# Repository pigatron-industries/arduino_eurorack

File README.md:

# Arduino Eurorack

Utilities for creating Eurorack modules using Arduino devices.

Tested with the following devices, but will likely work with any 3.3v logic level device (may require changes for a 5v logic level):

    Teensy LC / 4.0 / 4.1
    Electrosmith Daisy

## Documentation

[Documentation](https://pigatron-industries.github.io/arduino_eurorack/)

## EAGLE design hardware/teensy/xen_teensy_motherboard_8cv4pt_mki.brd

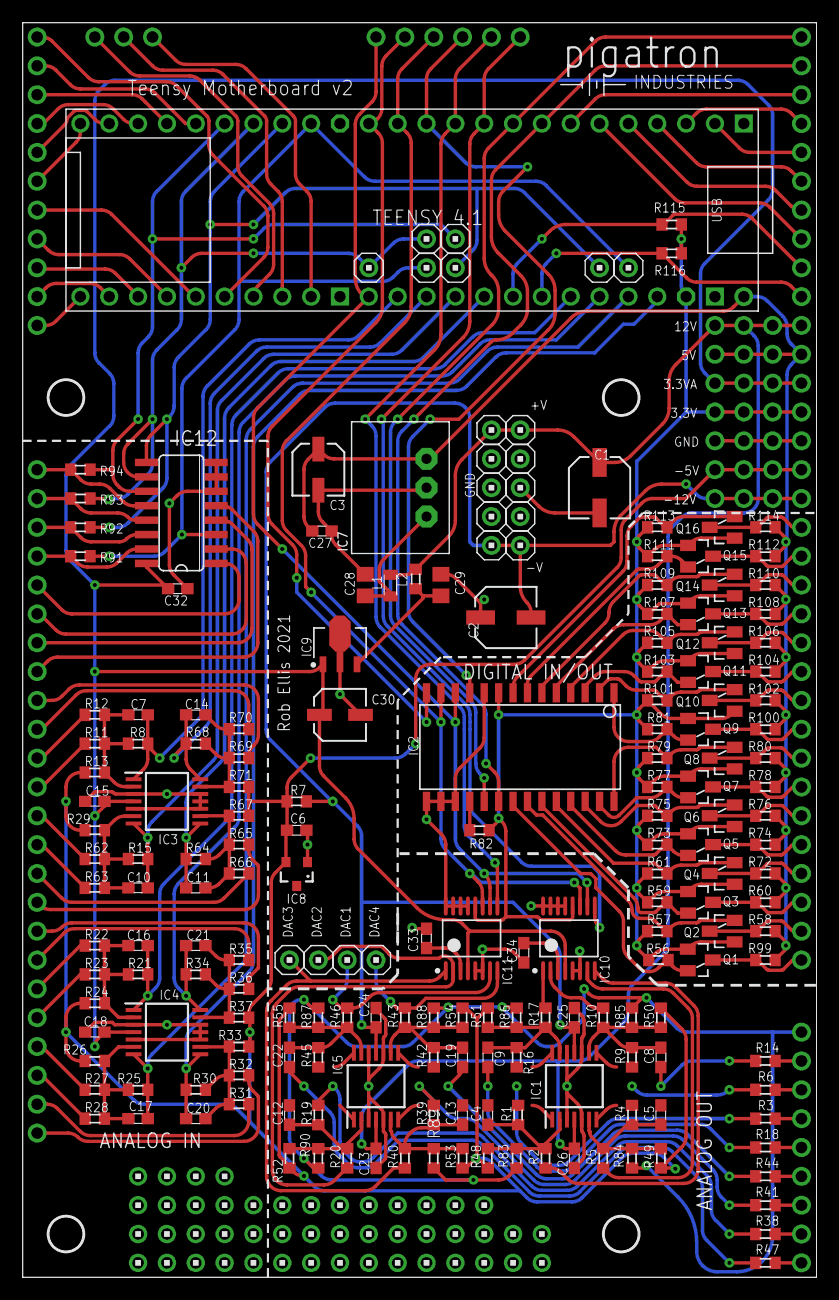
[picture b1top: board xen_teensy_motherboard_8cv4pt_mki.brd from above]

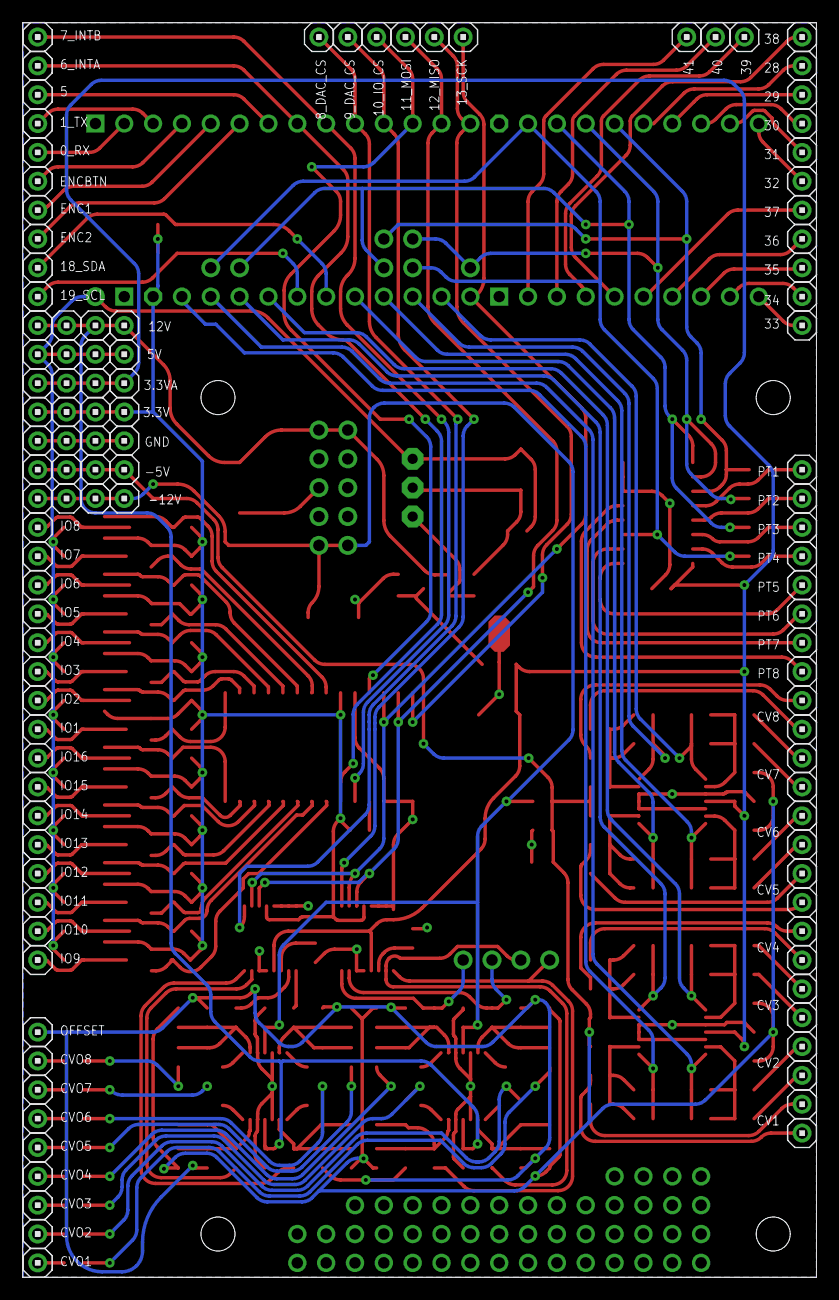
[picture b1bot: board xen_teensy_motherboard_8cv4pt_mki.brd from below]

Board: 2 copper layers, 69.9 x 110.5 mm, 355 parts (107 on the bottom side), 151 nets.

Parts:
0_RX, 1_TX, 3.3V, 3.3V1, 3.3V2, 3.3V3, 3.3VA, 3.3VA1, 3.3VA2, 3.3VA3, 5, 5V, 5V1, 5V2, 5V3, 6_INTA, 7_INTB, 8_DAC_CS, 9_DAC_CS, 10_IO_CS, 11_MOSI, 12_MISO, 13_SCK, 18_SDA, 19_SCL, 24_4.0-A10, 24_LC-A10, 25_4.0-A11, 25_LC-A11, 26_4.0-A12, 26_LC-A12, 27_4.0-A13, 28, 29, 30, 31, 32, 33, 34, 35, 36, 37, 38, 39, 40, 41: HEADER/MALE/01
+V, +V1, +V2, +V3, +V4, +V5: HEADER/MALE/01
-5V, -5V1, -5V2, -5V3: HEADER/MALE/01
-V, -V1, -V2, -V3, -V4, -V5: HEADER/MALE/01
C1, C2: 22uF; SV-C
C3, C30: 10uF; SV-B
C4, C5, C8, C9, C12, C13, C19, C22: 100pF; C0603
C6, C15, C18, C23, C24, C25, C26, C27, C32: 100nF; C0603
C7, C10, C11, C14, C16, C17, C20, C21: 1nF; C0603
C28, C29: 22uF; C0805
C33, C34: 470nF; C0603
CV1, CV1B, CV2, CV2B, CV3, CV3B, CV4, CV4B, CV5, CV5B, CV6, CV6B, CV7, CV7B, CV8, CV8B: HEADER/MALE/01
CVO1, CVO2, CVO3, CVO4, CVO5, CVO6, CVO7, CVO8: HEADER/MALE/01
DAC1, DAC2, DAC3, DAC4: HEADER/MALE/01
ENC1, ENC2: HEADER/MALE/01
ENCBTN: HEADER/MALE/01
GND, GND1, GND2, GND3, GND4, GND5, GND6, GND7, GND8, GND9: HEADER/MALE/01
IC1, IC5: TL074PW; TSSOP14
IC2: MCP23S17SO; SO28W
IC3, IC4: MCP6004; TSSOP14
IC6: TEENSY41-OUTER; TENNSY41-OUTER
IC7: R-78E5.0-0.5; WE78
IC8: LM4040-5V; SOT-23
IC9: 3.3V; LD2981-SOT89
IC10, IC11: DAC8164; TEXAS_INSTRUMENTS_DAC8164IBPWG4_1
IC12: CD4051CD4051_SO16; SO16
IO1, IO2, IO3, IO4, IO5, IO6, IO7, IO8, IO9, IO10, IO11, IO12, IO13, IO14, IO15, IO16: HEADER/MALE/01
L1: 33uH; L2012C
L2: R0603
OFFSET: HEADER/MALE/01
P1, P2, P3, P4, P5, P6, P7, P8, P9, P10, P11, P12, P13, P14, P15, P16, P17, P18, P19, P21, P22, P23, P24, P25, P26, P27, P28, P29, P30, P31, P32, P33, P34, P35, P36, P37, P38, P39, P40, P41, P42, P44, P45, P46, P47, P49, P50: HEADER/MALE/01NOBORDER; HEADER/MALE/01/NOBORDER
PT1, PT2, PT3, PT4, PT5, PT6, PT7, PT8: HEADER/MALE/01
Q1, Q2, Q3, Q4, Q5, Q6, Q7, Q8, Q9, Q10, Q11, Q12, Q13, Q14, Q15, Q16: BF170; SOT23
R1, R4, R9, R16, R19, R39, R42, R45, R48, R49, R50, R51, R52, R53, R54, R55, R83, R84, R85, R86, R87, R88, R89, R90: 120k; R0603
R2, R5, R10, R17, R20, R40, R43, R46: 30k; R0603
R3, R6, R14, R18, R38, R41, R44, R47, R82: 1k; R0603
R7, R115, R116: 2K; R0603
R8, R15, R21, R25, R30, R34, R64, R68: 33k; R0603
R11, R12, R13, R22, R23, R24, R26, R27, R28, R29, R31, R32, R33, R35, R36, R37, R62, R63, R65, R66, R67, R69, R70, R71: 100k; R0603
R56, R57, R58, R59, R60, R61, R72, R73, R74, R75, R76, R77, R78, R79, R80, R81, R99, R100, R101, R102, R103, R104, R105, R106, R107, R108, R109, R110, R111, R112, R113, R114: 10k; R0603
R91, R92, R93, R94: 0R; R0603
U$1: PIGATRON-LOGO
U$2, U$3, U$4, U$5: STANDOFF/3.0

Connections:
3.3V: 3.3V.1, 3.3V1.1, 3.3V2.1, 3.3V3.1, IC2.9, IC6.3V3-3, IC10.12, IC11.12, Q1.1, Q2.1, Q3.1, Q4.1, Q5.1, Q6.1, Q7.1, Q8.1, Q9.1, Q10.1, Q11.1, Q12.1, Q13.1, Q14.1, Q15.1, Q16.1, R56.2, R57.2, R59.2, R61.2, R73.2, R75.2, R77.2, R79.2, R81.2, R82.1, R101.2, R103.2, R105.2, R107.2, R109.2, R111.2, R113.2, R115.2, R116.2
3.3V_A: 3.3VA.1, 3.3VA1.1, 3.3VA2.1, 3.3VA3.1, C15.2, C18.2, C30.+, C32.2, IC3.4, IC4.4, IC9.1, IC10.4, IC11.4, IC12.16
5V: 5V.1, 5V1.1, 5V2.1, 5V3.1, C3.+, C27.2, IC6.VIN, IC7.3, R58.2, R60.2, R72.2, R74.2, R76.2, R78.2, R80.2, R99.2, R100.2, R102.2, R104.2, R106.2, R108.2, R110.2, R112.2, R114.2
+12V: +V.1, +V1.1, +V2.1, +V3.1, +V4.1, +V5.1, C1.+, C23.2, C26.2, IC1.4, IC5.4, L1.1, L2.1
-5VREF: -5V.1, -5V1.1, -5V2.1, -5V3.1, C6.2, IC8.2, R7.1, R13.1, R24.1, R26.1, R29.1, R33.1, R37.1, R48.1, R49.1, R50.1, R51.1, R52.1, R53.1, R54.1, R55.1, R67.1, R71.1
-12V: -V.1, -V1.1, -V2.1, -V3.1, -V4.1, -V5.1, C2.-, C24.1, C25.1, IC1.11, IC5.11, R7.2
ADC0: C7.2, IC3.1, IC6.14-A0/TX3/SPDIF_OUT, R8.2
ADC1: C14.2, IC3.14, IC6.15-A1/RX3/SPDIF_IN, R68.2
ADC2: C10.2, IC3.7, IC6.16-A2/RX4/SCL1, R15.2
ADC3: C11.2, IC3.8, IC6.17-A3/TX4/SDA1, R64.2
ADC4: C16.2, IC4.1, IC6.20-A6/TX5/LRCLK1, R21.2
ADC5: C21.2, IC4.14, IC6.21-A7/RX5/BCLK1, R34.2
ADC6: C17.2, IC4.7, IC6.22-A8/CTX1, R25.2
ADC7: C20.2, IC4.8, IC6.23-A9/CRX1/MCLK1, R30.2
ADC8: 24_4.0-A10.1, 24_LC-A10.1, IC6.24-A10/TX6/SCL2, IC12.3, R91.2
ADC9: 25_4.0-A11.1, 25_LC-A11.1, IC6.25-A11/RX6/SDA2, IC12.9, R92.2
ADC10: 26_4.0-A12.1, 26_LC-A12.1, IC6.26-A12/MOSI1, IC12.10, R93.2
ADC11: 27_4.0-A13.1, IC6.27-A13/SCK1, IC12.11, R94.2
DAC1: DAC1.1, IC11.7, R46.1
DAC2: DAC2.1, IC11.2, R20.1
DAC3: DAC4.1, IC11.8, R43.1
DAC4: DAC3.1, IC11.1, R40.1
DAC5: IC10.1, R17.1
DAC6: IC10.8, R2.1
DAC7: IC10.2, R10.1
DAC8: IC10.7, R5.1
GPA0: IC2.21, Q1.2, R56.1
GPA1: IC2.22, Q2.2, R57.1
GPA2: IC2.23, Q3.2, R59.1
GPA3: IC2.24, Q4.2, R61.1
GPA4: IC2.25, Q5.2, R73.1
GPA5: IC2.26, Q6.2, R75.1
GPA6: IC2.27, Q7.2, R77.1
GPA7: IC2.28, Q8.2, R79.1
GPB0: IC2.1, Q9.2, R81.1
GPB1: IC2.2, Q10.2, R101.1
GPB2: IC2.3, Q11.2, R103.1
GPB3: IC2.4, Q12.2, R105.1
GPB4: IC2.5, Q13.2, R107.1
GPB5: IC2.6, Q14.2, R109.1
GPB6: IC2.7, Q15.2, R111.1
GPB7: IC2.8, Q16.2, R113.1
INTA: 6_INTA.1, IC2.20, IC6.6-OUT1D
INTB: 7_INTB.1, IC2.19, IC6.7-RX2/OUT1A
unnamed: CV2.1, R27.1
unnamed: C4.1, IC1.2, R1.1, R2.2, R48.2, R83.2
unnamed: C4.2, IC1.1, R3.1
unnamed: CVO6.1, R1.2, R3.2
unnamed: C5.1, IC1.6, R4.1, R5.2, R49.2, R84.2
unnamed: C5.2, IC1.7, R6.1
unnamed: CVO7.1, R4.2, R6.2
unnamed: C7.1, IC3.2, R8.1, R11.2, R12.2, R13.2
unnamed: C8.1, IC1.9, R9.1, R10.2, R50.2, R85.2
unnamed: C8.2, IC1.8, R14.1
unnamed: CVO8.1, R9.2, R14.2
unnamed: C9.1, IC1.13, R16.1, R17.2, R51.2, R86.2
unnamed: CV7B.1, R12.1
unnamed: CV7.1, R11.1
unnamed: C9.2, IC1.14, R18.1
unnamed: C10.1, IC3.6, R15.1, R29.2, R62.2, R63.2
unnamed: CVO5.1, R16.2, R18.2
unnamed: CV6.1, R62.1
unnamed: CV6B.1, R63.1
unnamed: C12.1, IC5.2, R19.1, R20.2, R52.2, R90.2
unnamed: C12.2, IC5.1, R38.1
unnamed: CV3.1, R22.1
unnamed: 0_RX.1, IC6.0-RX1/CS1/CRX2
unnamed: C16.1, IC4.2, R21.1, R22.2, R23.2, R24.2
unnamed: CVO2.1, R19.2, R38.2
unnamed: CV2B.1, R28.1
unnamed: CV3B.1, R23.1
unnamed: C13.1, IC5.6, R39.1, R40.2, R53.2, R89.2
unnamed: C17.1, IC4.6, R25.1, R26.2, R27.2, R28.2
unnamed: C21.1, IC4.13, R34.1, R35.2, R36.2, R37.2
unnamed: CV4.1, R35.1
unnamed: CV4B.1, R36.1
unnamed: C13.2, IC5.7, R41.1
unnamed: CV1B.1, R32.1
unnamed: CV1.1, R31.1
unnamed: C20.1, IC4.9, R30.1, R31.2, R32.2, R33.2
unnamed: 1_TX.1, IC6.1-TX1/MISO1/CTX2
unnamed: ENC2.1, IC6.4-BCLK2
unnamed: ENC1.1, IC6.3-LRCLK2
unnamed: ENCBTN.1, IC6.2-OUT2
unnamed: IC12.1, PT5.1
unnamed: CVO3.1, R39.2, R41.2
unnamed: C19.1, IC5.9, R42.1, R43.2, R54.2, R88.2
unnamed: C19.2, IC5.8, R44.1
unnamed: 18_SDA.1, IC6.18-A4/SDA0, R115.1
unnamed: 19_SCL.1, IC6.19-A5/SCL0, R116.1
unnamed: CVO4.1, R42.2, R44.2
unnamed: C22.1, IC5.13, R45.1, R46.2, R55.2, R87.2
unnamed: C22.2, IC5.14, R47.1
unnamed: CVO1.1, R45.2, R47.2
unnamed: C28.2, IC7.1, L1.2
unnamed: IC12.5, PT8.1
unnamed: IO9.1, Q1.3, R99.1
unnamed: IC12.12, PT1.1, R94.1
unnamed: IO10.1, Q2.3, R58.1
unnamed: IC12.15, PT4.1, R91.1
unnamed: C14.1, IC3.13, R68.1, R69.2, R70.2, R71.2
unnamed: IO11.1, Q3.3, R60.1
unnamed: IC12.13, PT2.1, R93.1
unnamed: CV8.1, R69.1
unnamed: IO12.1, Q4.3, R72.1
unnamed: IC12.14, PT3.1, R92.1
unnamed: IO13.1, Q5.3, R74.1
unnamed: IC12.2, PT6.1
unnamed: IO14.1, Q6.3, R76.1
unnamed: IC12.4, PT7.1
unnamed: IO15.1, Q7.3, R78.1
unnamed: CV8B.1, R70.1
unnamed: CV5B.1, R66.1
unnamed: CV5.1, R65.1
unnamed: C11.1, IC3.9, R64.1, R65.2, R66.2, R67.2
unnamed: C29.2, IC9.3, L2.2
unnamed: IO16.1, Q8.3, R80.1
unnamed: IO1.1, Q9.3, R100.1
unnamed: IO2.1, Q10.3, R102.1
unnamed: IO3.1, Q11.3, R104.1
unnamed: IO4.1, Q12.3, R106.1
unnamed: IO5.1, Q13.3, R108.1
unnamed: IO6.1, Q14.3, R110.1
unnamed: IO7.1, Q15.3, R112.1
unnamed: IO8.1, Q16.3, R114.1
unnamed: IC2.18, R82.2
unnamed: 5.1, IC6.5-IN2
unnamed: C34.1, IC10.3
unnamed: 28.1, IC6.28-RX7
unnamed: 29.1, IC6.29-TX7
unnamed: 30.1, IC6.30-CRX3
unnamed: 31.1, IC6.31-CTX3
unnamed: 32.1, IC6.32-OUT1B
unnamed: 41.1, IC6.41-A17/MISO1
unnamed: 40.1, IC6.40-A16/CS1
unnamed: 39.1, IC6.39-A15/CS/OUT1A
unnamed: 38.1, IC6.38-A14/CS/IN1
unnamed: C33.1, IC11.3
unnamed: 34.1, IC6.34-RX8
unnamed: 35.1, IC6.35-TX8
unnamed: 33.1, IC6.33-MCLK2
unnamed: 36.1, IC6.36-PWM
unnamed: 37.1, IC6.37-PWM
OFFSET: OFFSET.1, R83.1, R84.1, R85.1, R86.1, R87.1, R88.1, R89.1, R90.1
PE: C1.-, C2.+, C3.-, C6.1, C15.1, C18.1, C23.1, C24.2, C25.2, C26.1, C27.1, C28.1, C29.1, C30.-, C32.1, C33.2, C34.2, GND.1, GND1.1, GND2.1, GND3.1, GND4.1, GND5.1, GND6.1, GND7.1, GND8.1, GND9.1, IC1.3, IC1.5, IC1.10, IC1.12, IC2.10, IC2.15, IC2.16, IC2.17, IC3.3, IC3.5, IC3.10, IC3.11, IC3.12, IC4.3, IC4.5, IC4.10, IC4.11, IC4.12, IC5.3, IC5.5, IC5.10, IC5.12, IC6.GND1, IC6.GND3, IC6.GND6, IC7.2, IC8.1, IC9.2, IC9.2-2, IC10.5, IC10.6, IC10.13, IC10.14, IC10.15, IC10.16, IC11.5, IC11.6, IC11.13, IC11.14, IC11.15, IC11.16, IC12.6, IC12.7, IC12.8
SPI_CS_DAC1: 9_DAC_CS.1, IC6.9-OUT1C, IC11.9
SPI_CS_DAC2: 8_DAC_CS.1, IC6.8-TX2/IN1, IC10.9
SPI_IO_CS: 10_IO_CS.1, IC2.11, IC6.10-CS\MQSR
SPI_MISO: 12_MISO.1, IC2.14, IC6.12-MISO/MQSL
SPI_MOSI: 11_MOSI.1, IC2.13, IC6.11-MOSI/CTX1, IC10.11, IC11.11
SPI_SCK: 13_SCK.1, IC2.12, IC6.13-SCK/LED, IC10.10, IC11.10

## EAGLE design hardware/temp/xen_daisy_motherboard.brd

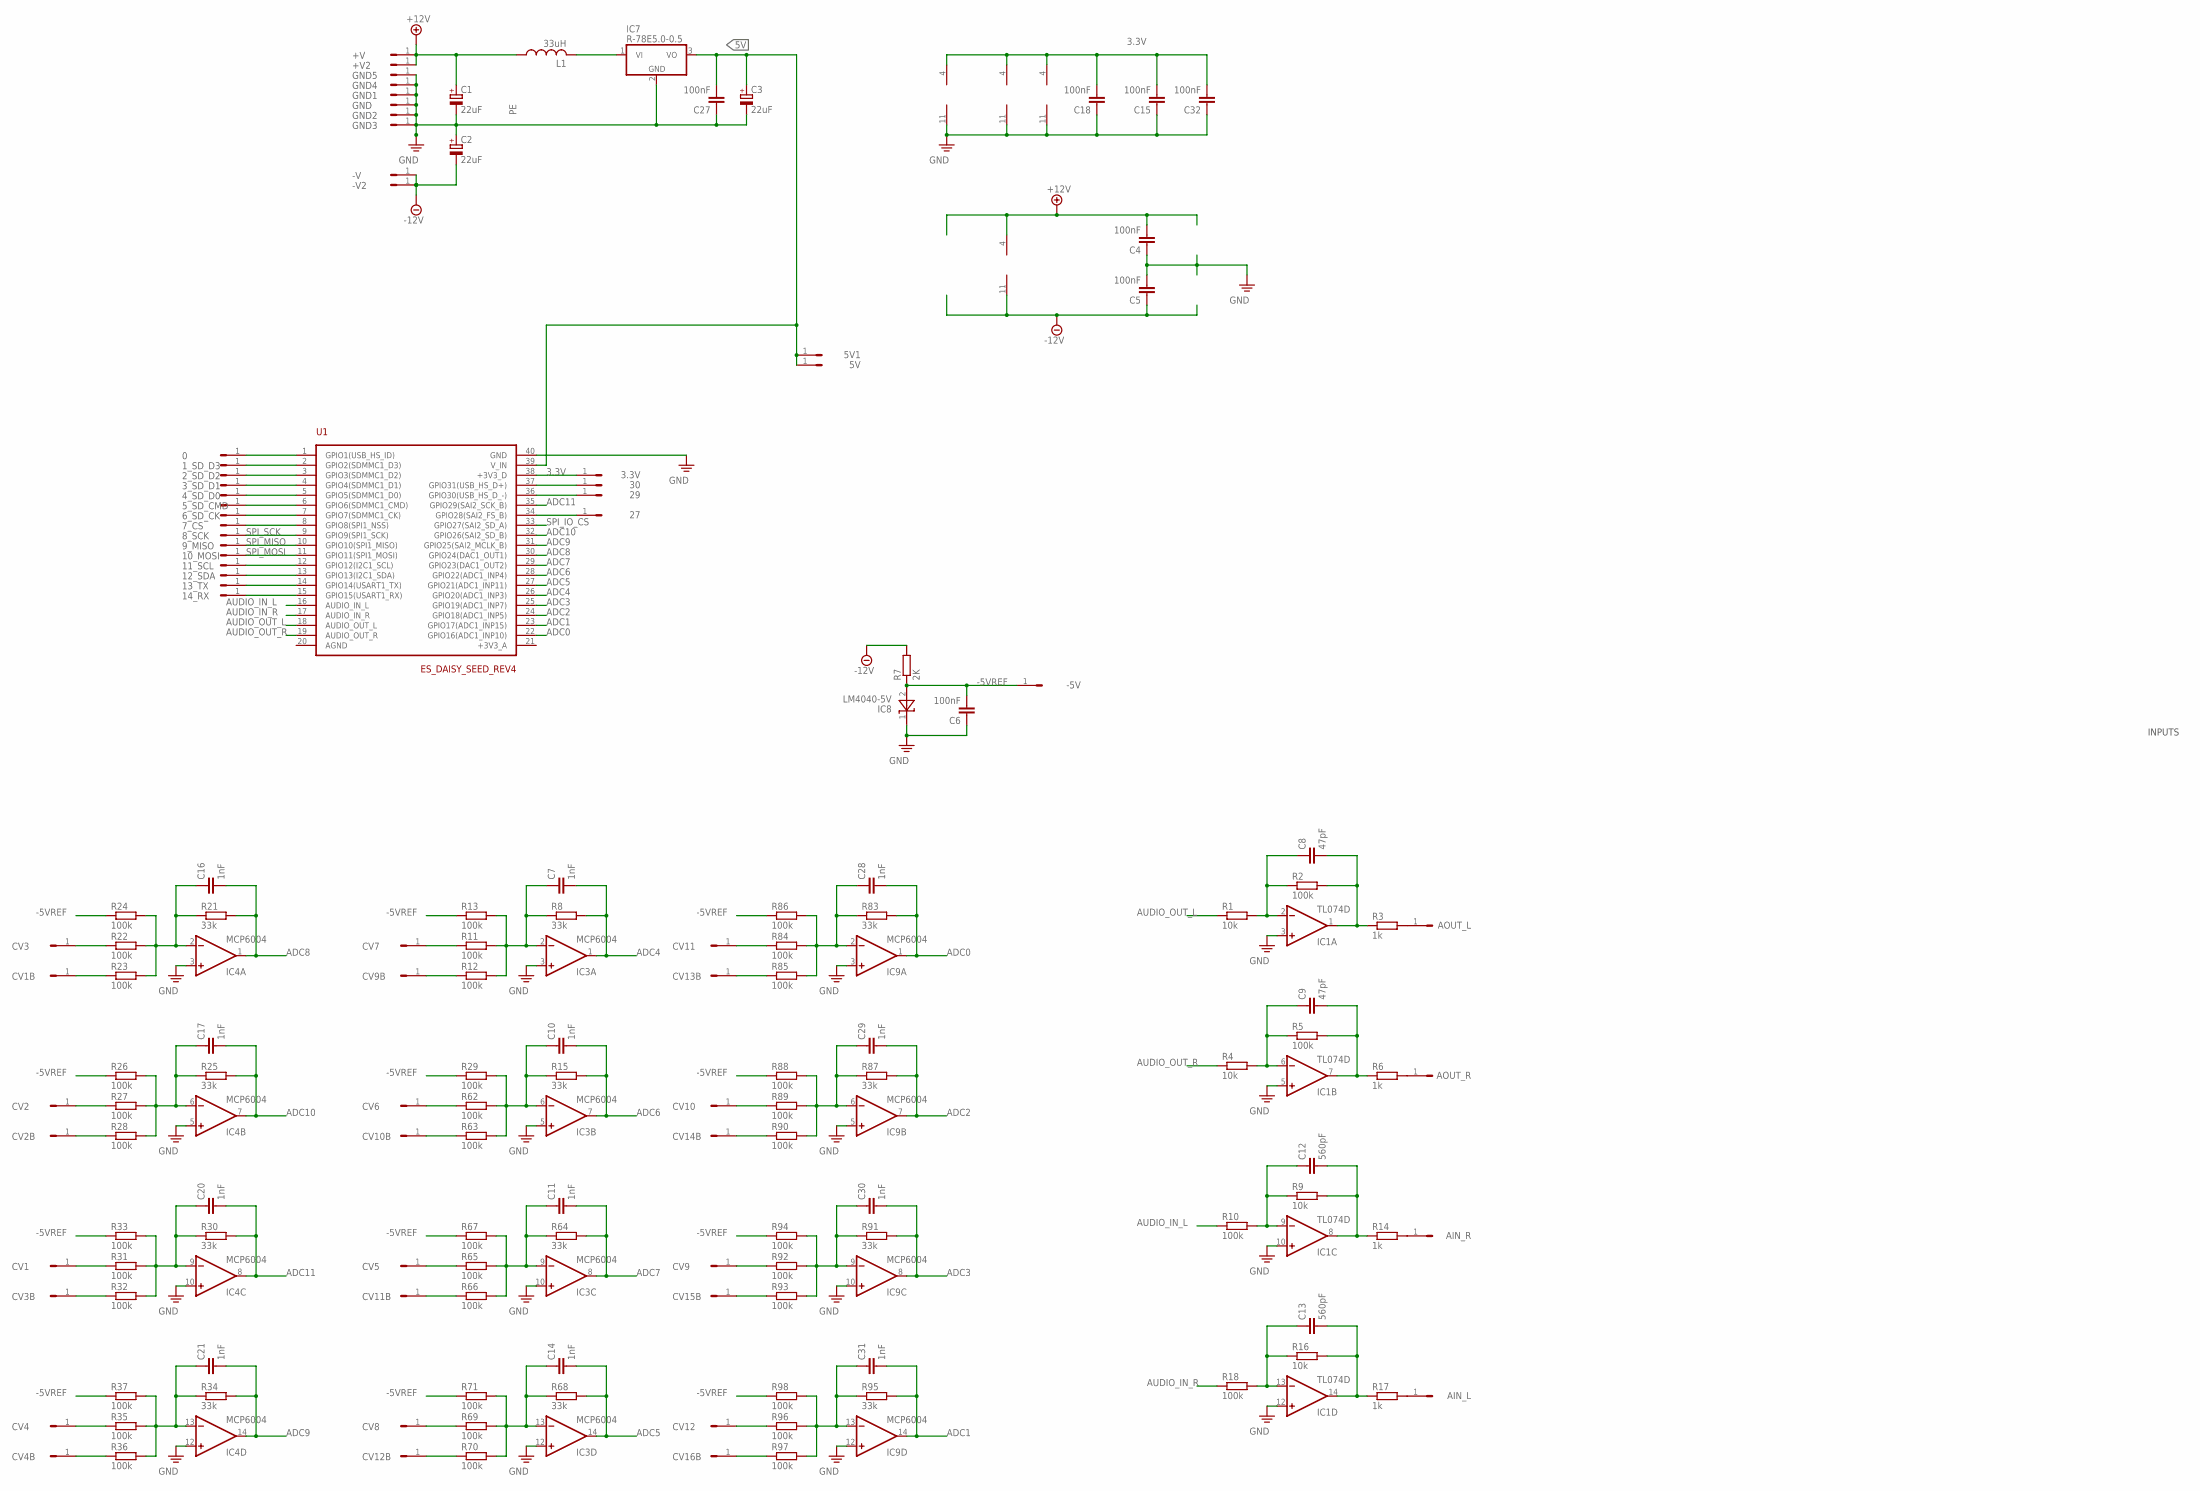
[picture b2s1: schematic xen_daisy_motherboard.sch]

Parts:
0, 1_SD_D3, 2_SD_D2, 3.3V, 3_SD_D1, 4_SD_D0, 5V, 5V1, 5_SD_CMD, 6_SD_CK, 7_CS, 8_SCK, 9_MISO, 10_MOSI, 11_SCL, 12_SDA, 13_TX, 14_RX, 27, 29, 30: HEADER/MALE/01
+V, +V2: HEADER/MALE/01
-5V: HEADER/MALE/01
-V, -V2: HEADER/MALE/01
AIN_L: HEADER/MALE/01
AIN_R: HEADER/MALE/01
AOUT_L: HEADER/MALE/01
AOUT_R: HEADER/MALE/01
C1, C2, C3: 22uF; PANASONIC_A
C4, C5, C6, C15, C18, C27, C32: 100nF; C0603
C7, C10, C11, C14, C16, C17, C20, C21, C28, C29, C30, C31: 1nF; C0603
C8, C9: 47pF; C0603
C12, C13: 560pF; C0603
CV1, CV1B, CV2, CV2B, CV3, CV3B, CV4, CV4B, CV5, CV6, CV7, CV8, CV9, CV9B, CV10, CV10B, CV11, CV11B, CV12, CV12B, CV13B, CV14B, CV15B, CV16B: HEADER/MALE/01
GND, GND1, GND2, GND3, GND4, GND5: HEADER/MALE/01
IC1: TL074D; SO14
IC3, IC4, IC9: MCP6004; SO14
IC7: R-78E5.0-0.5; WE78
IC8: LM4040-5V; SOT-23
L1: 33uH; L2012C
R1, R4, R9, R16: 10k; R0603
R2, R5, R10, R11, R12, R13, R18, R22, R23, R24, R26, R27, R28, R29, R31, R32, R33, R35, R36, R37, R62, R63, R65, R66, R67, R69, R70, R71, R84, R85, R86, R88, R89, R90, R92, R93, R94, R96, R97, R98: 100k; R0603
R3, R6, R14, R17: 1k; R0603
R7: 2K; R0603
R8, R15, R21, R25, R30, R34, R64, R68, R83, R87, R91, R95: 33k; R0603
U1: ES_DAISY_SEED_REV4; ES_DAISY_SEED

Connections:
3.3V: 3.3V.1, C15.2, C18.2, C32.2, IC3.4 (V+), IC4.4 (V+), IC9.4 (V+), U1.38 (+3V3_D)
5V: 5V.1, 5V1.1, C3.+, C27.2, IC7.3 (VO), U1.39 (V_IN)
+12V: +V.1, +V2.1, C1.+, C4.2, IC1.4 (V+), L1.1
-5VREF: -5V.1, C6.2, IC8.2 (A), R7.1, R13.1, R24.1, R26.1, R29.1, R33.1, R37.1, R67.1, R71.1, R86.1, R88.1, R94.1, R98.1
-12V: -V.1, -V2.1, C2.-, C5.1, IC1.11 (V-), R7.2
ADC0: C28.2, IC9.1 (OUT), R83.2, U1.22 (GPIO16(ADC1_INP10))
ADC1: C31.2, IC9.14 (OUT), R95.2, U1.23 (GPIO17(ADC1_INP15))
ADC2: C29.2, IC9.7 (OUT), R87.2, U1.24 (GPIO18(ADC1_INP5))
ADC3: C30.2, IC9.8 (OUT), R91.2, U1.25 (GPIO19(ADC1_INP7))
ADC4: C7.2, IC3.1 (OUT), R8.2, U1.26 (GPIO20(ADC1_INP3))
ADC5: C14.2, IC3.14 (OUT), R68.2, U1.27 (GPIO21(ADC1_INP11))
ADC6: C10.2, IC3.7 (OUT), R15.2, U1.28 (GPIO22(ADC1_INP4))
ADC7: C11.2, IC3.8 (OUT), R64.2, U1.29 (GPIO23(DAC1_OUT2))
ADC8: C16.2, IC4.1 (OUT), R21.2, U1.30 (GPIO24(DAC1_OUT1))
ADC9: C21.2, IC4.14 (OUT), R34.2, U1.31 (GPIO25(SAI2_MCLK_B))
ADC10: C17.2, IC4.7 (OUT), R25.2, U1.32 (GPIO26(SAI2_SD_B))
ADC11: C20.2, IC4.8 (OUT), R30.2, U1.35 (GPIO29(SAI2_SCK_B))
AUDIO_IN_L: R10.1, U1.16 (AUDIO_IN_L)
AUDIO_IN_R: R18.1, U1.17 (AUDIO_IN_R)
AUDIO_OUT_L: R1.1, U1.18 (AUDIO_OUT_L)
AUDIO_OUT_R: R4.1, U1.19 (AUDIO_OUT_R)
unnamed: CV2.1, R27.1
unnamed: C8.1, IC1.2 (-IN), R1.2, R2.1
unnamed: C8.2, IC1.1 (OUT), R2.2, R3.1
unnamed: C9.1, IC1.6 (-IN), R4.2, R5.1
unnamed: AOUT_L.1, R3.2
unnamed: C9.2, IC1.7 (OUT), R5.2, R6.1
unnamed: AIN_R.1, R14.2
unnamed: C7.1, IC3.2 (-IN), R8.1, R11.2, R12.2, R13.2
unnamed: AOUT_R.1, R6.2
unnamed: C12.1, IC1.9 (-IN), R9.1, R10.2
unnamed: CV9B.1, R12.1
unnamed: CV7.1, R11.1
unnamed: C13.1, IC1.13 (-IN), R16.1, R18.2
unnamed: C10.1, IC3.6 (-IN), R15.1, R29.2, R62.2, R63.2
unnamed: C13.2, IC1.14 (OUT), R16.2, R17.1
unnamed: CV6.1, R62.1
unnamed: CV10B.1, R63.1
unnamed: C12.2, IC1.8 (OUT), R9.2, R14.1
unnamed: CV3.1, R22.1
unnamed: C16.1, IC4.2 (-IN), R21.1, R22.2, R23.2, R24.2
unnamed: AIN_L.1, R17.2
unnamed: CV2B.1, R28.1
unnamed: CV1B.1, R23.1
unnamed: C17.1, IC4.6 (-IN), R25.1, R26.2, R27.2, R28.2
unnamed: C21.1, IC4.13 (-IN), R34.1, R35.2, R36.2, R37.2
unnamed: CV4.1, R35.1
unnamed: CV4B.1, R36.1
unnamed: CV3B.1, R32.1
unnamed: CV1.1, R31.1
unnamed: C20.1, IC4.9 (-IN), R30.1, R31.2, R32.2, R33.2
unnamed: 27.1, U1.34 (GPIO28(SAI2_FS_B))
unnamed: 13_TX.1, U1.14 (GPIO14(USART1_TX))
unnamed: 14_RX.1, U1.15 (GPIO15(USART1_RX))
unnamed: 30.1, U1.37 (GPIO31(USB_HS_D+))
unnamed: 6_SD_CK.1, U1.7 (GPIO7(SDMMC1_CK))
unnamed: 12_SDA.1, U1.13 (GPIO13(I2C1_SDA))
unnamed: 11_SCL.1, U1.12 (GPIO12(I2C1_SCL))
unnamed: IC7.1 (VI), L1.2
unnamed: C14.1, IC3.13 (-IN), R68.1, R69.2, R70.2, R71.2
unnamed: CV8.1, R69.1
unnamed: CV12B.1, R70.1
unnamed: CV11B.1, R66.1
unnamed: CV5.1, R65.1
unnamed: C11.1, IC3.9 (-IN), R64.1, R65.2, R66.2, R67.2
unnamed: 29.1, U1.36 (GPIO30(USB_HS_D_-))
unnamed: C28.1, IC9.2 (-IN), R83.1, R84.2, R85.2, R86.2
unnamed: CV13B.1, R85.1
unnamed: CV11.1, R84.1
unnamed: C29.1, IC9.6 (-IN), R87.1, R88.2, R89.2, R90.2
unnamed: CV10.1, R89.1
unnamed: CV14B.1, R90.1
unnamed: C31.1, IC9.13 (-IN), R95.1, R96.2, R97.2, R98.2
unnamed: CV12.1, R96.1
unnamed: CV16B.1, R97.1
unnamed: CV15B.1, R93.1
unnamed: CV9.1, R92.1
unnamed: C30.1, IC9.9 (-IN), R91.1, R92.2, R93.2, R94.2
unnamed: 7_CS.1, U1.8 (GPIO8(SPI1_NSS))
unnamed: 5_SD_CMD.1, U1.6 (GPIO6(SDMMC1_CMD))
unnamed: 4_SD_D0.1, U1.5 (GPIO5(SDMMC1_D0))
unnamed: 3_SD_D1.1, U1.4 (GPIO4(SDMMC1_D1))
unnamed: 2_SD_D2.1, U1.3 (GPIO3(SDMMC1_D2))
unnamed: 1_SD_D3.1, U1.2 (GPIO2(SDMMC1_D3))
unnamed: 0.1, U1.1 (GPIO1(USB_HS_ID))
PE: C1.-, C2.+, C3.-, C4.1, C5.2, C6.1, C15.1, C18.1, C27.1, C32.1, GND.1, GND1.1, GND2.1, GND3.1, GND4.1, GND5.1, IC1.3 (+IN), IC1.5 (+IN), IC1.10 (+IN), IC1.12 (+IN), IC3.3 (+IN), IC3.5 (+IN), IC3.10 (+IN), IC3.11 (V-), IC3.12 (+IN), IC4.3 (+IN), IC4.5 (+IN), IC4.10 (+IN), IC4.11 (V-), IC4.12 (+IN), IC7.2 (GND), IC8.1 (C), IC9.3 (+IN), IC9.5 (+IN), IC9.10 (+IN), IC9.11 (V-), IC9.12 (+IN), U1.40 (GND)
SPI_IO_CS: U1.33 (GPIO27(SAI2_SD_A))
SPI_MISO: 9_MISO.1, U1.10 (GPIO10(SPI1_MISO))
SPI_MOSI: 10_MOSI.1, U1.11 (GPIO11(SPI1_MOSI))
SPI_SCK: 8_SCK.1, U1.9 (GPIO9(SPI1_SCK))

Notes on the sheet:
INPUTS

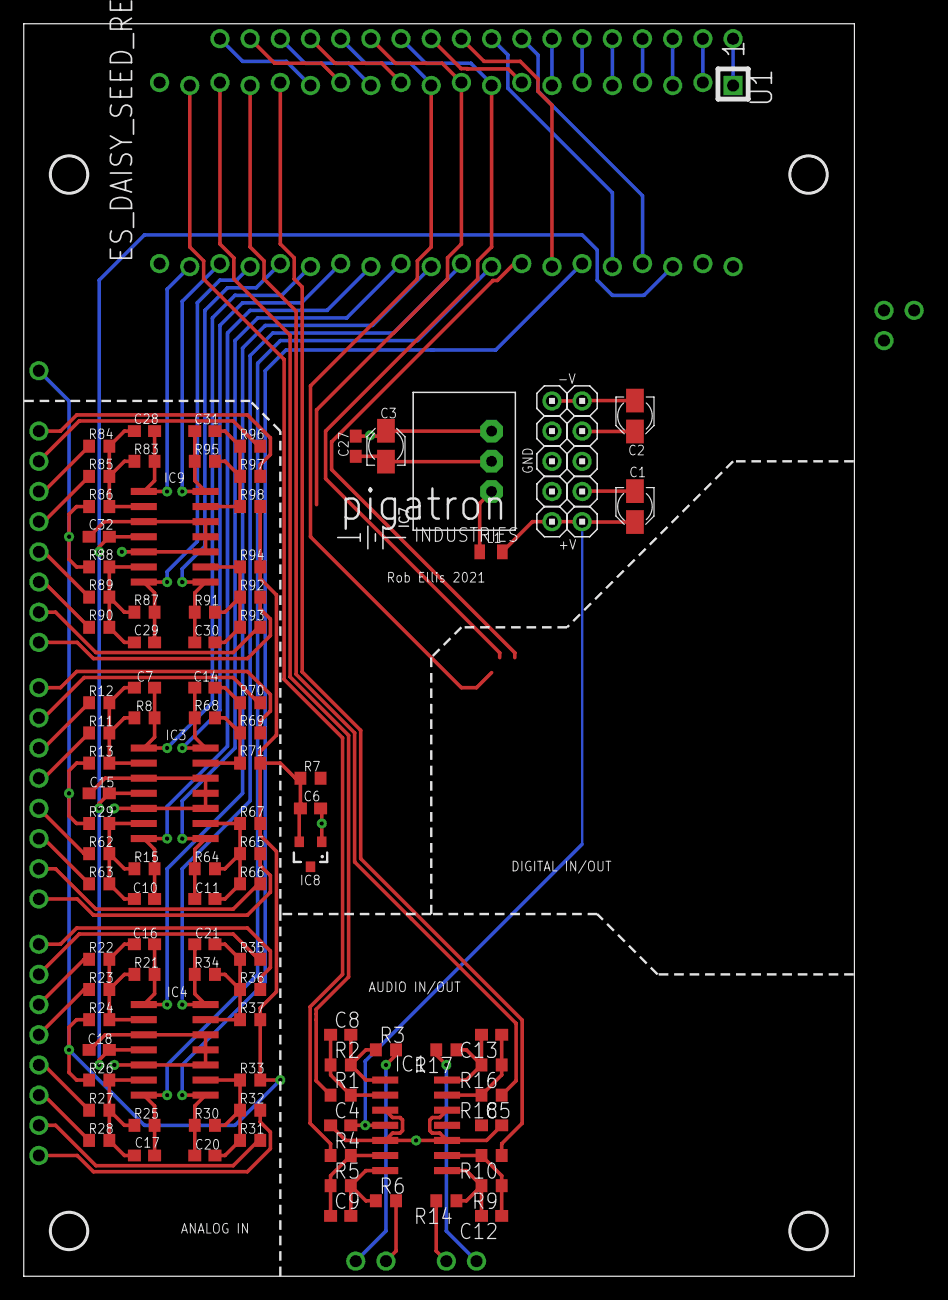
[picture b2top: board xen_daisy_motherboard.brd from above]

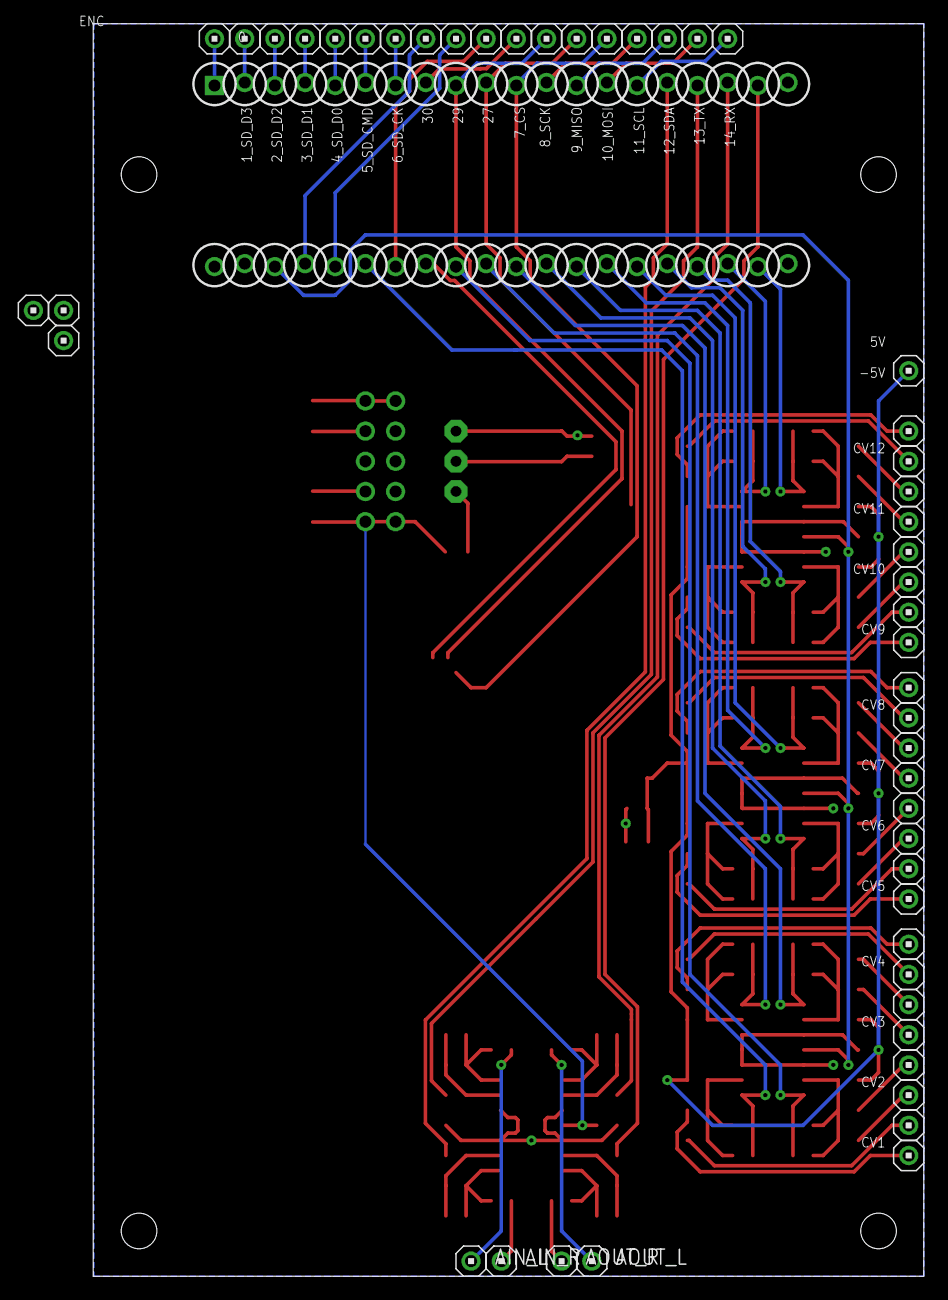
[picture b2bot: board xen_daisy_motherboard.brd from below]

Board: 2 copper layers, 69.9 x 105.4 mm, 160 parts (50 on the bottom side), 89 nets.

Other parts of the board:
U$1: PIGATRON-LOGO
U$2, U$3, U$4, U$5: STANDOFF/3.0
